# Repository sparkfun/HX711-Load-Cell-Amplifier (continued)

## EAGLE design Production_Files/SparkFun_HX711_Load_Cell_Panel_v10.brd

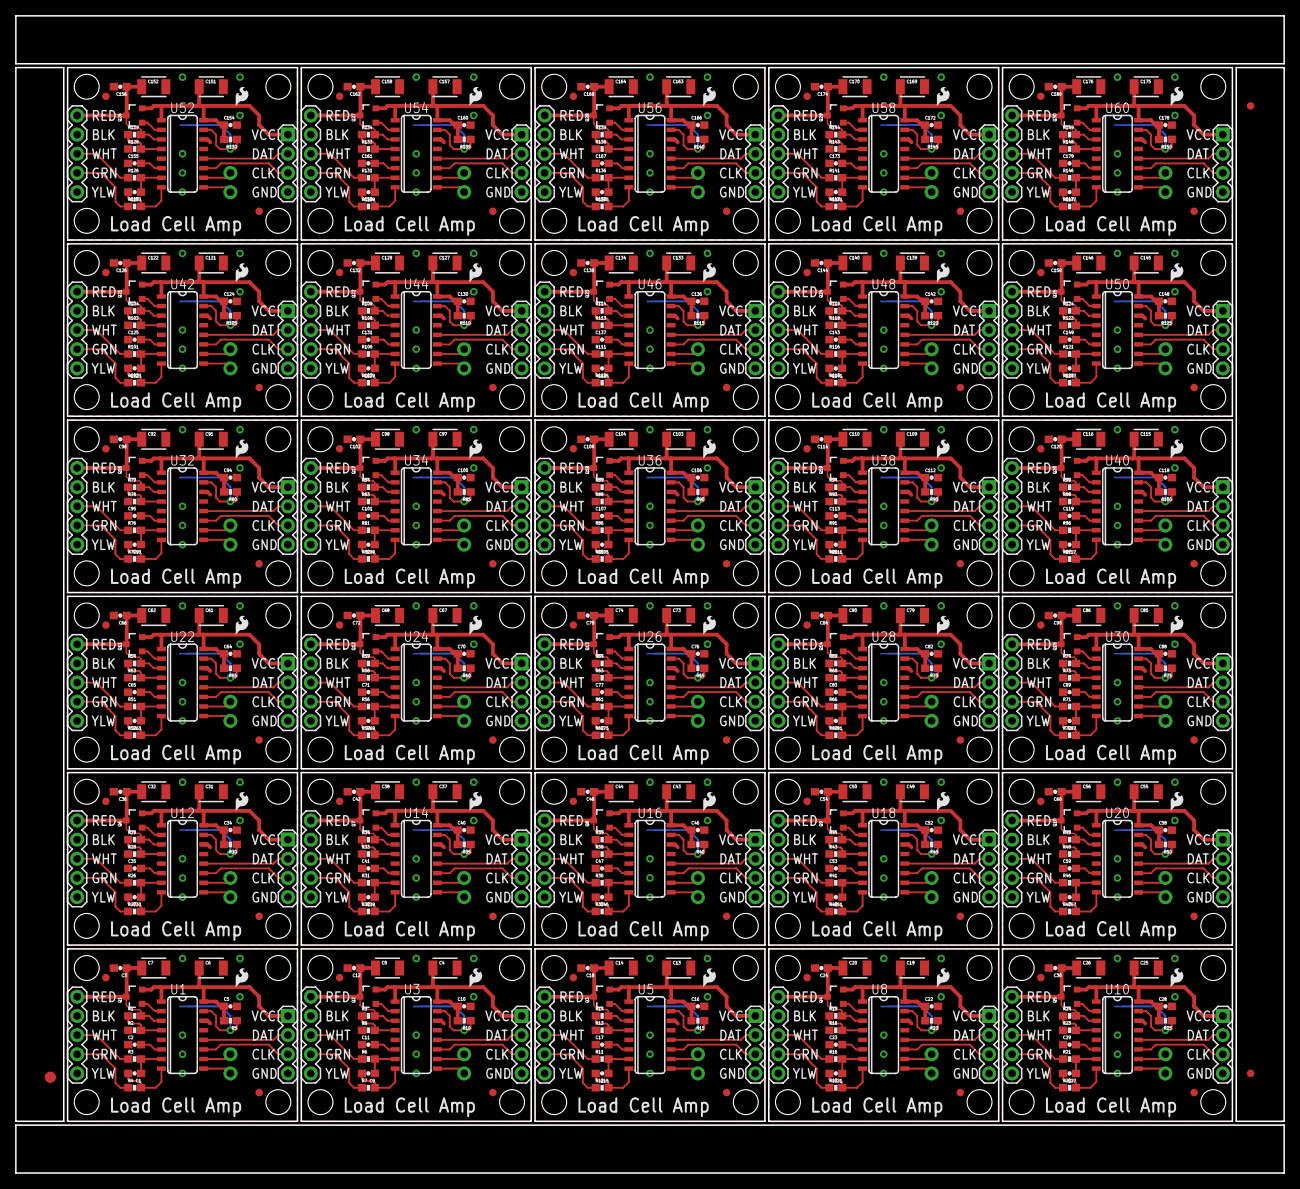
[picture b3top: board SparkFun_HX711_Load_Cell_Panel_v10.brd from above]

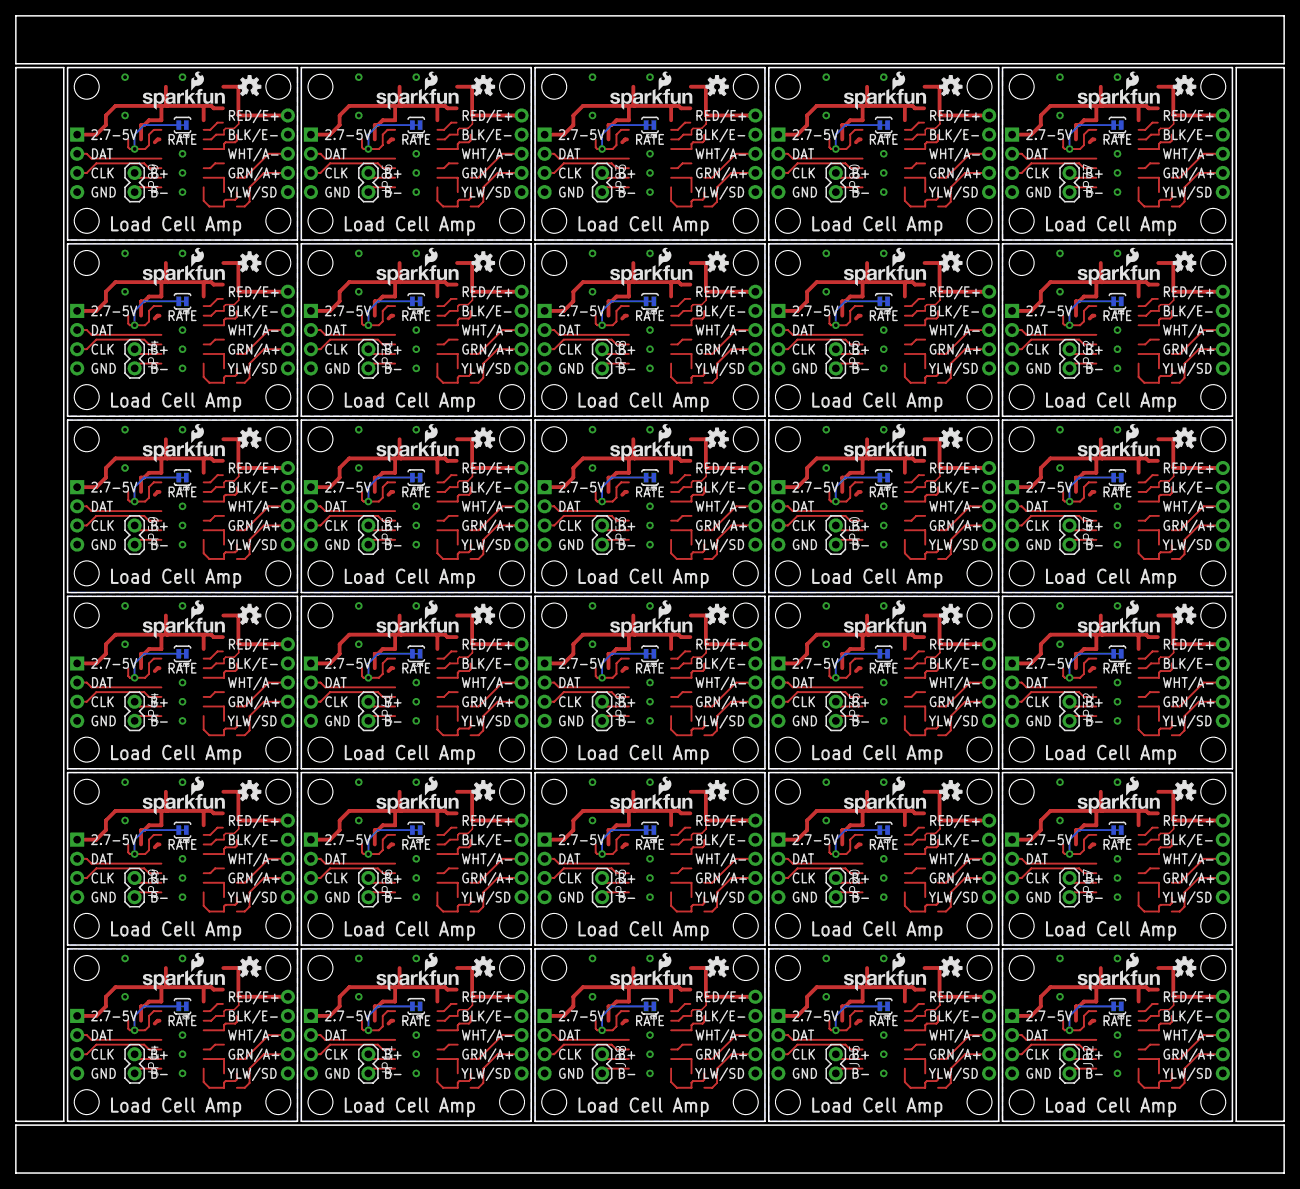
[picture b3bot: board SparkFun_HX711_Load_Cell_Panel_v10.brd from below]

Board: 2 copper layers, 168.1 x 153.4 mm, 783 parts (120 on the bottom side), 450 nets.

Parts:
C1, C2, C3, C5, C9, C10, C11, C12, C15, C16, C17, C18, C21, C22, C23, C24, C27, C28, C29, C30, C33, C34, C35, C36, C39, C40, C41, C42, C45, C46, C47, C48, C51, C52, C53, C54, C57, C58, C59, C60, C63, C64, C65, C66, C69, C70, C71, C72, C75, C76, C77, C78, C81, C82, C83, C84, C87, C88, C89, C90, C93, C94, C95, C96, C99, C100, C101, C102, C105, C106, C107, C108, C111, C112, C113, C114, C117, C118, C119, C120, C123, C124, C125, C126, C129, C130, C131, C132, C135, C136, C137, C138, C141, C142, C143, C144, C147, C148, C149, C150, C153, C154, C155, C156, C159, C160, C161, C162, C165, C166, C167, C168, C171, C172, C173, C174, C177, C178, C179, C180: 0.1uF; 0603-CAP
C4, C6, C7, C8, C13, C14, C19, C20, C25, C26, C31, C32, C37, C38, C43, C44, C49, C50, C55, C56, C61, C62, C67, C68, C73, C74, C79, C80, C85, C86, C91, C92, C97, C98, C103, C104, C109, C110, C115, C116, C121, C122, C127, C128, C133, C134, C139, C140, C145, C146, C151, C152, C157, C158, C163, C164, C169, C170, C175, C176: 10uF; 1210
E$1: FIDUCIAL-1.5X3
E$4, E$5: FIDUCIAL-1X2
FID1, FID2, FID3, FID4, FID5, FID6, FID7, FID8, FID9, FID10, FID11, FID12, FID13, FID14, FID15, FID16, FID17, FID18, FID19, FID20, FID21, FID22, FID23, FID24, FID25, FID26, FID27, FID28, FID29, FID30, FID31, FID32, FID33, FID34, FID35, FID36, FID37, FID38, FID39, FID40, FID41, FID42, FID43, FID44, FID45, FID46, FID47, FID48, FID49, FID50, FID51, FID52, FID53, FID54, FID55, FID56, FID57, FID58, FID59, FID60: FIDUCIAL1X2; FIDUCIAL-1X2
JP1, JP3, JP7, JP10, JP13, JP16, JP19, JP22, JP25, JP28, JP31, JP34, JP37, JP40, JP43, JP46, JP49, JP52, JP55, JP58, JP61, JP64, JP67, JP70, JP73, JP76, JP79, JP82, JP85, JP88: 1X04
JP2, JP5, JP8, JP11, JP14, JP17, JP20, JP23, JP26, JP29, JP32, JP35, JP38, JP41, JP44, JP47, JP50, JP53, JP56, JP59, JP62, JP65, JP68, JP71, JP74, JP77, JP80, JP83, JP86, JP89: 1X02
JP4, JP6, JP9, JP12, JP15, JP18, JP21, JP24, JP27, JP30, JP33, JP36, JP39, JP42, JP45, JP48, JP51, JP54, JP57, JP60, JP63, JP66, JP69, JP72, JP75, JP78, JP81, JP84, JP87, JP90: 1X05
LOGO1, LOGO2, LOGO5, LOGO7, LOGO9, LOGO11, LOGO13, LOGO15, LOGO17, LOGO19, LOGO21, LOGO23, LOGO25, LOGO27, LOGO29, LOGO31, LOGO33, LOGO35, LOGO37, LOGO39, LOGO41, LOGO43, LOGO45, LOGO47, LOGO49, LOGO51, LOGO53, LOGO55, LOGO57, LOGO59: SFE_LOGO_NAME_FLAME.1_INCH; SFE_LOGO_NAME_FLAME_.1
LOGO3, LOGO4, LOGO6, LOGO8, LOGO10, LOGO12, LOGO14, LOGO16, LOGO18, LOGO20, LOGO22, LOGO24, LOGO26, LOGO28, LOGO30, LOGO32, LOGO34, LOGO36, LOGO38, LOGO40, LOGO42, LOGO44, LOGO46, LOGO48, LOGO50, LOGO52, LOGO54, LOGO56, LOGO58, LOGO60: SFE_LOGO_FLAME.1_INCH; SFE_LOGO_FLAME_.1
Q1, Q2, Q3, Q4, Q5, Q6, Q7, Q8, Q9, Q10, Q11, Q12, Q13, Q14, Q15, Q16, Q17, Q18, Q19, Q20, Q21, Q22, Q23, Q24, Q25, Q26, Q27, Q28, Q29, Q30: MMBT4403; SOT23-3
R1, R9, R14, R19, R24, R29, R34, R39, R44, R49, R54, R59, R64, R69, R74, R79, R84, R89, R94, R99, R104, R109, R114, R119, R124, R129, R134, R139, R144, R149: 20K; 0603-RES
R2, R8, R13, R18, R23, R28, R33, R38, R43, R48, R53, R58, R63, R68, R73, R78, R83, R88, R93, R98, R103, R108, R113, R118, R123, R128, R133, R138, R143, R148: 8.2K; 0603-RES
R3, R4, R6, R7, R11, R12, R16, R17, R21, R22, R26, R27, R31, R32, R36, R37, R41, R42, R46, R47, R51, R52, R56, R57, R61, R62, R66, R67, R71, R72, R76, R77, R81, R82, R86, R87, R91, R92, R96, R97, R101, R102, R106, R107, R111, R112, R116, R117, R121, R122, R126, R127, R131, R132, R136, R137, R141, R142, R146, R147: 100; 0603-RES
R5, R10, R15, R20, R25, R30, R35, R40, R45, R50, R55, R60, R65, R70, R75, R80, R85, R90, R95, R100, R105, R110, R115, R120, R125, R130, R135, R140, R145, R150: 10K; 0603-RES
SJ1, SJ2, SJ3, SJ4, SJ5, SJ6, SJ7, SJ8, SJ9, SJ10, SJ11, SJ12, SJ13, SJ14, SJ15, SJ16, SJ17, SJ18, SJ19, SJ20, SJ21, SJ22, SJ23, SJ24, SJ25, SJ26, SJ27, SJ28, SJ29, SJ30: PAD-JUMPER-2-NC_BY_TRACE_YES_SILK
STANDOFF1, STANDOFF2, STANDOFF3, STANDOFF4, STANDOFF5, STANDOFF6, STANDOFF7, STANDOFF8, STANDOFF9, STANDOFF10, STANDOFF11, STANDOFF12, STANDOFF13, STANDOFF14, STANDOFF15, STANDOFF16, STANDOFF17, STANDOFF18, STANDOFF19, STANDOFF20, STANDOFF21, STANDOFF22, STANDOFF23, STANDOFF24, STANDOFF25, STANDOFF26, STANDOFF27, STANDOFF28, STANDOFF29, STANDOFF30, STANDOFF31, STANDOFF32, STANDOFF33, STANDOFF34, STANDOFF35, STANDOFF36, STANDOFF37, STANDOFF38, STANDOFF39, STANDOFF40, STANDOFF41, STANDOFF42, STANDOFF43, STANDOFF44, STANDOFF45, STANDOFF46, STANDOFF47, STANDOFF48, STANDOFF49, STANDOFF50, STANDOFF51, STANDOFF52, STANDOFF53, STANDOFF54, STANDOFF55, STANDOFF56, STANDOFF57, STANDOFF58, STANDOFF59, STANDOFF60, STANDOFF61, STANDOFF62, STANDOFF63, STANDOFF64, STANDOFF65, STANDOFF66, STANDOFF67, STANDOFF68, STANDOFF69, STANDOFF70, STANDOFF71, STANDOFF72, STANDOFF73, STANDOFF74, STANDOFF75, STANDOFF76, STANDOFF77, STANDOFF78, STANDOFF79, STANDOFF80, STANDOFF81, STANDOFF82, STANDOFF83, STANDOFF84, STANDOFF85, STANDOFF86, STANDOFF87, STANDOFF88, STANDOFF89, STANDOFF90, STANDOFF91, STANDOFF92, STANDOFF93, STANDOFF94, STANDOFF95, STANDOFF96, STANDOFF97, STANDOFF98, STANDOFF99, STANDOFF100, STANDOFF101, STANDOFF102, STANDOFF103, STANDOFF104, STANDOFF105, STANDOFF106, STANDOFF107, STANDOFF108, STANDOFF109, STANDOFF110, STANDOFF111, STANDOFF112, STANDOFF113, STANDOFF114, STANDOFF115, STANDOFF116, STANDOFF117, STANDOFF118, STANDOFF119, STANDOFF120: STAND-OFF
U1, U3, U5, U8, U10, U12, U14, U16, U18, U20, U22, U24, U26, U28, U30, U32, U34, U36, U38, U40, U42, U44, U46, U48, U50, U52, U54, U56, U58, U60: HX711; SO16
U2, U4, U6, U7, U9, U11, U13, U15, U17, U19, U21, U23, U25, U27, U29, U31, U33, U35, U37, U39, U41, U43, U45, U47, U49, U51, U53, U55, U57, U59: OSHW-LOGOS; OSHW-LOGO-S

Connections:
A+: JP4.2, R4.1
A+1: JP6.2, R7.1
A+2: JP9.2, R12.1
A+3: JP12.2, R17.1
A+4: JP15.2, R22.1
A+5: JP18.2, R27.1
A+6: JP21.2, R32.1
A+7: JP24.2, R37.1
A+8: JP27.2, R42.1
A+9: JP30.2, R47.1
A+10: JP33.2, R52.1
A+11: JP36.2, R57.1
A+12: JP39.2, R62.1
A+13: JP42.2, R67.1
A+14: JP45.2, R72.1
A+15: JP48.2, R77.1
A+16: JP51.2, R82.1
A+17: JP54.2, R87.1
A+18: JP57.2, R92.1
A+19: JP60.2, R97.1
A+20: JP63.2, R102.1
A+21: JP66.2, R107.1
A+22: JP69.2, R112.1
A+23: JP72.2, R117.1
A+24: JP75.2, R122.1
A+25: JP78.2, R127.1
A+26: JP81.2, R132.1
A+27: JP84.2, R137.1
A+28: JP87.2, R142.1
A+29: JP90.2, R147.1
A-: JP4.3, R3.1
A-1: JP6.3, R6.1
A-2: JP9.3, R11.1
A-3: JP12.3, R16.1
A-4: JP15.3, R21.1
A-5: JP18.3, R26.1
A-6: JP21.3, R31.1
A-7: JP24.3, R36.1
A-8: JP27.3, R41.1
A-9: JP30.3, R46.1
A-10: JP33.3, R51.1
A-11: JP36.3, R56.1
A-12: JP39.3, R61.1
A-13: JP42.3, R66.1
A-14: JP45.3, R71.1
A-15: JP48.3, R76.1
A-16: JP51.3, R81.1
A-17: JP54.3, R86.1
A-18: JP57.3, R91.1
A-19: JP60.3, R96.1
A-20: JP63.3, R101.1
A-21: JP66.3, R106.1
A-22: JP69.3, R111.1
A-23: JP72.3, R116.1
A-24: JP75.3, R121.1
A-25: JP78.3, R126.1
A-26: JP81.3, R131.1
A-27: JP84.3, R136.1
A-28: JP87.3, R141.1
A-29: JP90.3, R146.1
AVDD: C3.1, C7.1, JP4.5, Q1.3, R1.2, U1.3
AVDD1: C8.1, C12.1, JP6.5, Q2.3, R9.2, U3.3
AVDD2: C14.1, C18.1, JP9.5, Q3.3, R14.2, U5.3
AVDD3: C20.1, C24.1, JP12.5, Q4.3, R19.2, U8.3
AVDD4: C26.1, C30.1, JP15.5, Q5.3, R24.2, U10.3
AVDD5: C32.1, C36.1, JP18.5, Q6.3, R29.2, U12.3
AVDD6: C38.1, C42.1, JP21.5, Q7.3, R34.2, U14.3
AVDD7: C44.1, C48.1, JP24.5, Q8.3, R39.2, U16.3
AVDD8: C50.1, C54.1, JP27.5, Q9.3, R44.2, U18.3
AVDD9: C56.1, C60.1, JP30.5, Q10.3, R49.2, U20.3
AVDD10: C62.1, C66.1, JP33.5, Q11.3, R54.2, U22.3
AVDD11: C68.1, C72.1, JP36.5, Q12.3, R59.2, U24.3
AVDD12: C74.1, C78.1, JP39.5, Q13.3, R64.2, U26.3
AVDD13: C80.1, C84.1, JP42.5, Q14.3, R69.2, U28.3
AVDD14: C86.1, C90.1, JP45.5, Q15.3, R74.2, U30.3
AVDD15: C92.1, C96.1, JP48.5, Q16.3, R79.2, U32.3
AVDD16: C98.1, C102.1, JP51.5, Q17.3, R84.2, U34.3
AVDD17: C104.1, C108.1, JP54.5, Q18.3, R89.2, U36.3
AVDD18: C110.1, C114.1, JP57.5, Q19.3, R94.2, U38.3
AVDD19: C116.1, C120.1, JP60.5, Q20.3, R99.2, U40.3
AVDD20: C122.1, C126.1, JP63.5, Q21.3, R104.2, U42.3
AVDD21: C128.1, C132.1, JP66.5, Q22.3, R109.2, U44.3
AVDD22: C134.1, C138.1, JP69.5, Q23.3, R114.2, U46.3
AVDD23: C140.1, C144.1, JP72.5, Q24.3, R119.2, U48.3
AVDD24: C146.1, C150.1, JP75.5, Q25.3, R124.2, U50.3
AVDD25: C152.1, C156.1, JP78.5, Q26.3, R129.2, U52.3
AVDD26: C158.1, C162.1, JP81.5, Q27.3, R134.2, U54.3
AVDD27: C164.1, C168.1, JP84.5, Q28.3, R139.2, U56.3
AVDD28: C170.1, C174.1, JP87.5, Q29.3, R144.2, U58.3
AVDD29: C176.1, C180.1, JP90.5, Q30.3, R149.2, U60.3
B+: JP2.1, U1.10
B+1: JP5.1, U3.10
B+2: JP8.1, U5.10
B+3: JP11.1, U8.10
B+4: JP14.1, U10.10
B+5: JP17.1, U12.10
B+6: JP20.1, U14.10
B+7: JP23.1, U16.10
B+8: JP26.1, U18.10
B+9: JP29.1, U20.10
B+10: JP32.1, U22.10
B+11: JP35.1, U24.10
B+12: JP38.1, U26.10
B+13: JP41.1, U28.10
B+14: JP44.1, U30.10
B+15: JP47.1, U32.10
B+16: JP50.1, U34.10
B+17: JP53.1, U36.10
B+18: JP56.1, U38.10
B+19: JP59.1, U40.10
B+20: JP62.1, U42.10
B+21: JP65.1, U44.10
B+22: JP68.1, U46.10
B+23: JP71.1, U48.10
B+24: JP74.1, U50.10
B+25: JP77.1, U52.10
B+26: JP80.1, U54.10
B+27: JP83.1, U56.10
B+28: JP86.1, U58.10
B+29: JP89.1, U60.10
B-: JP2.2, U1.9
B-1: JP5.2, U3.9
B-2: JP8.2, U5.9
B-3: JP11.2, U8.9
B-4: JP14.2, U10.9
B-5: JP17.2, U12.9
B-6: JP20.2, U14.9
B-7: JP23.2, U16.9
B-8: JP26.2, U18.9
B-9: JP29.2, U20.9
B-10: JP32.2, U22.9
B-11: JP35.2, U24.9
B-12: JP38.2, U26.9
B-13: JP41.2, U28.9
B-14: JP44.2, U30.9
B-15: JP47.2, U32.9
B-16: JP50.2, U34.9
B-17: JP53.2, U36.9
B-18: JP56.2, U38.9
B-19: JP59.2, U40.9
B-20: JP62.2, U42.9
B-21: JP65.2, U44.9
B-22: JP68.2, U46.9
B-23: JP71.2, U48.9
B-24: JP74.2, U50.9
B-25: JP77.2, U52.9
B-26: JP80.2, U54.9
B-27: JP83.2, U56.9
B-28: JP86.2, U58.9
B-29: JP89.2, U60.9
DAT: JP1.2, U1.12
DAT1: JP3.2, U3.12
DAT2: JP7.2, U5.12
DAT3: JP10.2, U8.12
DAT4: JP13.2, U10.12
DAT5: JP16.2, U12.12
DAT6: JP19.2, U14.12
DAT7: JP22.2, U16.12
DAT8: JP25.2, U18.12
DAT9: JP28.2, U20.12
DAT10: JP31.2, U22.12
DAT11: JP34.2, U24.12
DAT12: JP37.2, U26.12
DAT13: JP40.2, U28.12
DAT14: JP43.2, U30.12
DAT15: JP46.2, U32.12
DAT16: JP49.2, U34.12
DAT17: JP52.2, U36.12
DAT18: JP55.2, U38.12
DAT19: JP58.2, U40.12
DAT20: JP61.2, U42.12
DAT21: JP64.2, U44.12
DAT22: JP67.2, U46.12
DAT23: JP70.2, U48.12
DAT24: JP73.2, U50.12
DAT25: JP76.2, U52.12
DAT26: JP79.2, U54.12
DAT27: JP82.2, U56.12
DAT28: JP85.2, U58.12
DAT29: JP88.2, U60.12
GND: C2.1, C3.2, C5.2, C6.2, C7.2, JP1.4, JP4.1, JP4.4, R2.1, SJ2.1, U1.5, U1.14
GND1: C4.2, C8.2, C10.2, C11.1, C12.2, JP3.4, JP6.1, JP6.4, R8.1, SJ1.1, U3.5, U3.14
GND2: C13.2, C14.2, C16.2, C17.1, C18.2, JP7.4, JP9.1, JP9.4, R13.1, SJ3.1, U5.5, U5.14
GND3: C19.2, C20.2, C22.2, C23.1, C24.2, JP10.4, JP12.1, JP12.4, R18.1, SJ4.1, U8.5, U8.14
GND4: C25.2, C26.2, C28.2, C29.1, C30.2, JP13.4, JP15.1, JP15.4, R23.1, SJ5.1, U10.5, U10.14
GND5: C31.2, C32.2, C34.2, C35.1, C36.2, JP16.4, JP18.1, JP18.4, R28.1, SJ6.1, U12.5, U12.14
GND6: C37.2, C38.2, C40.2, C41.1, C42.2, JP19.4, JP21.1, JP21.4, R33.1, SJ7.1, U14.5, U14.14
GND7: C43.2, C44.2, C46.2, C47.1, C48.2, JP22.4, JP24.1, JP24.4, R38.1, SJ8.1, U16.5, U16.14
GND8: C49.2, C50.2, C52.2, C53.1, C54.2, JP25.4, JP27.1, JP27.4, R43.1, SJ9.1, U18.5, U18.14
GND9: C55.2, C56.2, C58.2, C59.1, C60.2, JP28.4, JP30.1, JP30.4, R48.1, SJ10.1, U20.5, U20.14
GND10: C61.2, C62.2, C64.2, C65.1, C66.2, JP31.4, JP33.1, JP33.4, R53.1, SJ11.1, U22.5, U22.14
GND11: C67.2, C68.2, C70.2, C71.1, C72.2, JP34.4, JP36.1, JP36.4, R58.1, SJ12.1, U24.5, U24.14
GND12: C73.2, C74.2, C76.2, C77.1, C78.2, JP37.4, JP39.1, JP39.4, R63.1, SJ13.1, U26.5, U26.14
GND13: C79.2, C80.2, C82.2, C83.1, C84.2, JP40.4, JP42.1, JP42.4, R68.1, SJ14.1, U28.5, U28.14
GND14: C85.2, C86.2, C88.2, C89.1, C90.2, JP43.4, JP45.1, JP45.4, R73.1, SJ15.1, U30.5, U30.14
GND15: C91.2, C92.2, C94.2, C95.1, C96.2, JP46.4, JP48.1, JP48.4, R78.1, SJ16.1, U32.5, U32.14
GND16: C97.2, C98.2, C100.2, C101.1, C102.2, JP49.4, JP51.1, JP51.4, R83.1, SJ17.1, U34.5, U34.14
GND17: C103.2, C104.2, C106.2, C107.1, C108.2, JP52.4, JP54.1, JP54.4, R88.1, SJ18.1, U36.5, U36.14
GND18: C109.2, C110.2, C112.2, C113.1, C114.2, JP55.4, JP57.1, JP57.4, R93.1, SJ19.1, U38.5, U38.14
GND19: C115.2, C116.2, C118.2, C119.1, C120.2, JP58.4, JP60.1, JP60.4, R98.1, SJ20.1, U40.5, U40.14
GND20: C121.2, C122.2, C124.2, C125.1, C126.2, JP61.4, JP63.1, JP63.4, R103.1, SJ21.1, U42.5, U42.14
GND21: C127.2, C128.2, C130.2, C131.1, C132.2, JP64.4, JP66.1, JP66.4, R108.1, SJ22.1, U44.5, U44.14
GND22: C133.2, C134.2, C136.2, C137.1, C138.2, JP67.4, JP69.1, JP69.4, R113.1, SJ23.1, U46.5, U46.14
GND23: C139.2, C140.2, C142.2, C143.1, C144.2, JP70.4, JP72.1, JP72.4, R118.1, SJ24.1, U48.5, U48.14
GND24: C145.2, C146.2, C148.2, C149.1, C150.2, JP73.4, JP75.1, JP75.4, R123.1, SJ25.1, U50.5, U50.14
GND25: C151.2, C152.2, C154.2, C155.1, C156.2, JP76.4, JP78.1, JP78.4, R128.1, SJ26.1, U52.5, U52.14
GND26: C157.2, C158.2, C160.2, C161.1, C162.2, JP79.4, JP81.1, JP81.4, R133.1, SJ27.1, U54.5, U54.14
GND27: C163.2, C164.2, C166.2, C167.1, C168.2, JP82.4, JP84.1, JP84.4, R138.1, SJ28.1, U56.5, U56.14
GND28: C169.2, C170.2, C172.2, C173.1, C174.2, JP85.4, JP87.1, JP87.4, R143.1, SJ29.1, U58.5, U58.14
GND29: C175.2, C176.2, C178.2, C179.1, C180.2, JP88.4, JP90.1, JP90.4, R148.1, SJ30.1, U60.5, U60.14
unnamed: R5.1, SJ2.2, U1.15
unnamed: C1.1, R3.2, U1.7
unnamed: C1.2, R4.2, U1.8
unnamed: Q1.1, U1.2
unnamed: Q2.1, U3.2
unnamed: R1.1, R2.2, U1.4
unnamed: C2.2, U1.6
unnamed: R8.2, R9.1, U3.4
unnamed: C11.2, U3.6
unnamed: R10.1, SJ1.2, U3.15
unnamed: C9.1, R6.2, U3.7
unnamed: C9.2, R7.2, U3.8
unnamed: Q3.1, U5.2
unnamed: R13.2, R14.1, U5.4
unnamed: C17.2, U5.6
unnamed: R15.1, SJ3.2, U5.15
unnamed: C15.1, R11.2, U5.7
unnamed: C15.2, R12.2, U5.8
unnamed: Q4.1, U8.2
unnamed: R18.2, R19.1, U8.4
unnamed: C23.2, U8.6
unnamed: R20.1, SJ4.2, U8.15
unnamed: C21.1, R16.2, U8.7
unnamed: C21.2, R17.2, U8.8
unnamed: Q5.1, U10.2
unnamed: R23.2, R24.1, U10.4
unnamed: C29.2, U10.6
unnamed: R25.1, SJ5.2, U10.15
unnamed: C27.1, R21.2, U10.7
unnamed: C27.2, R22.2, U10.8
unnamed: Q6.1, U12.2
unnamed: R28.2, R29.1, U12.4
unnamed: C35.2, U12.6
unnamed: R30.1, SJ6.2, U12.15
unnamed: C33.1, R26.2, U12.7
unnamed: C33.2, R27.2, U12.8
unnamed: Q7.1, U14.2
unnamed: R33.2, R34.1, U14.4
unnamed: C41.2, U14.6
unnamed: R35.1, SJ7.2, U14.15
unnamed: C39.1, R31.2, U14.7
unnamed: C39.2, R32.2, U14.8
unnamed: Q8.1, U16.2
unnamed: R38.2, R39.1, U16.4
unnamed: C47.2, U16.6
unnamed: R40.1, SJ8.2, U16.15
unnamed: C45.1, R36.2, U16.7
unnamed: C45.2, R37.2, U16.8
unnamed: Q9.1, U18.2
unnamed: R43.2, R44.1, U18.4
unnamed: C53.2, U18.6
unnamed: R45.1, SJ9.2, U18.15
unnamed: C51.1, R41.2, U18.7
unnamed: C51.2, R42.2, U18.8
unnamed: Q10.1, U20.2
unnamed: R48.2, R49.1, U20.4
unnamed: C59.2, U20.6
unnamed: R50.1, SJ10.2, U20.15
unnamed: C57.1, R46.2, U20.7
unnamed: C57.2, R47.2, U20.8
unnamed: Q11.1, U22.2
unnamed: R53.2, R54.1, U22.4
unnamed: C65.2, U22.6
unnamed: R55.1, SJ11.2, U22.15
unnamed: C63.1, R51.2, U22.7
unnamed: C63.2, R52.2, U22.8
unnamed: Q12.1, U24.2
unnamed: R58.2, R59.1, U24.4
unnamed: C71.2, U24.6
unnamed: R60.1, SJ12.2, U24.15
unnamed: C69.1, R56.2, U24.7
unnamed: C69.2, R57.2, U24.8
unnamed: Q13.1, U26.2
unnamed: R63.2, R64.1, U26.4
unnamed: C77.2, U26.6
unnamed: R65.1, SJ13.2, U26.15
unnamed: C75.1, R61.2, U26.7
unnamed: C75.2, R62.2, U26.8
unnamed: Q14.1, U28.2
unnamed: R68.2, R69.1, U28.4
unnamed: C83.2, U28.6
unnamed: R70.1, SJ14.2, U28.15
unnamed: C81.1, R66.2, U28.7
unnamed: C81.2, R67.2, U28.8
unnamed: Q15.1, U30.2
unnamed: R73.2, R74.1, U30.4
unnamed: C89.2, U30.6
unnamed: R75.1, SJ15.2, U30.15
unnamed: C87.1, R71.2, U30.7
unnamed: C87.2, R72.2, U30.8
unnamed: Q16.1, U32.2
unnamed: R78.2, R79.1, U32.4
unnamed: C95.2, U32.6
unnamed: R80.1, SJ16.2, U32.15
unnamed: C93.1, R76.2, U32.7
unnamed: C93.2, R77.2, U32.8
unnamed: Q17.1, U34.2
unnamed: R83.2, R84.1, U34.4
unnamed: C101.2, U34.6
unnamed: R85.1, SJ17.2, U34.15
unnamed: C99.1, R81.2, U34.7
unnamed: C99.2, R82.2, U34.8
unnamed: Q18.1, U36.2
unnamed: R88.2, R89.1, U36.4
unnamed: C107.2, U36.6
unnamed: R90.1, SJ18.2, U36.15
unnamed: C105.1, R86.2, U36.7
unnamed: C105.2, R87.2, U36.8
unnamed: Q19.1, U38.2
unnamed: R93.2, R94.1, U38.4
unnamed: C113.2, U38.6
unnamed: R95.1, SJ19.2, U38.15
unnamed: C111.1, R91.2, U38.7
unnamed: C111.2, R92.2, U38.8
unnamed: Q20.1, U40.2
unnamed: R98.2, R99.1, U40.4
unnamed: C119.2, U40.6
unnamed: R100.1, SJ20.2, U40.15
unnamed: C117.1, R96.2, U40.7
unnamed: C117.2, R97.2, U40.8
unnamed: Q21.1, U42.2
unnamed: R103.2, R104.1, U42.4
unnamed: C125.2, U42.6
unnamed: R105.1, SJ21.2, U42.15
unnamed: C123.1, R101.2, U42.7
unnamed: C123.2, R102.2, U42.8
unnamed: Q22.1, U44.2
unnamed: R108.2, R109.1, U44.4
unnamed: C131.2, U44.6
unnamed: R110.1, SJ22.2, U44.15
unnamed: C129.1, R106.2, U44.7
unnamed: C129.2, R107.2, U44.8
unnamed: Q23.1, U46.2
unnamed: R113.2, R114.1, U46.4
unnamed: C137.2, U46.6
unnamed: R115.1, SJ23.2, U46.15
unnamed: C135.1, R111.2, U46.7
unnamed: C135.2, R112.2, U46.8
unnamed: Q24.1, U48.2
unnamed: R118.2, R119.1, U48.4
unnamed: C143.2, U48.6
unnamed: R120.1, SJ24.2, U48.15
unnamed: C141.1, R116.2, U48.7
unnamed: C141.2, R117.2, U48.8
unnamed: Q25.1, U50.2
unnamed: R123.2, R124.1, U50.4
unnamed: C149.2, U50.6
unnamed: R125.1, SJ25.2, U50.15
unnamed: C147.1, R121.2, U50.7
unnamed: C147.2, R122.2, U50.8
unnamed: Q26.1, U52.2
unnamed: R128.2, R129.1, U52.4
unnamed: C155.2, U52.6
unnamed: R130.1, SJ26.2, U52.15
unnamed: C153.1, R126.2, U52.7
unnamed: C153.2, R127.2, U52.8
unnamed: Q27.1, U54.2
unnamed: R133.2, R134.1, U54.4
unnamed: C161.2, U54.6
unnamed: R135.1, SJ27.2, U54.15
unnamed: C159.1, R131.2, U54.7
unnamed: C159.2, R132.2, U54.8
unnamed: Q28.1, U56.2
unnamed: R138.2, R139.1, U56.4
unnamed: C167.2, U56.6
unnamed: R140.1, SJ28.2, U56.15
unnamed: C165.1, R136.2, U56.7
unnamed: C165.2, R137.2, U56.8
unnamed: Q29.1, U58.2
unnamed: R143.2, R144.1, U58.4
unnamed: C173.2, U58.6
unnamed: R145.1, SJ29.2, U58.15
unnamed: C171.1, R141.2, U58.7
unnamed: C171.2, R142.2, U58.8
unnamed: Q30.1, U60.2
unnamed: R148.2, R149.1, U60.4
unnamed: C179.2, U60.6
unnamed: R150.1, SJ30.2, U60.15
unnamed: C177.1, R146.2, U60.7
unnamed: C177.2, R147.2, U60.8
SCK: JP1.3, U1.11
SCK1: JP3.3, U3.11
SCK2: JP7.3, U5.11
SCK3: JP10.3, U8.11
SCK4: JP13.3, U10.11
SCK5: JP16.3, U12.11
SCK6: JP19.3, U14.11
SCK7: JP22.3, U16.11
SCK8: JP25.3, U18.11
SCK9: JP28.3, U20.11
SCK10: JP31.3, U22.11
SCK11: JP34.3, U24.11
SCK12: JP37.3, U26.11
SCK13: JP40.3, U28.11
SCK14: JP43.3, U30.11
SCK15: JP46.3, U32.11
SCK16: JP49.3, U34.11
SCK17: JP52.3, U36.11
SCK18: JP55.3, U38.11
SCK19: JP58.3, U40.11
SCK20: JP61.3, U42.11
SCK21: JP64.3, U44.11
SCK22: JP67.3, U46.11
SCK23: JP70.3, U48.11
SCK24: JP73.3, U50.11
SCK25: JP76.3, U52.11
SCK26: JP79.3, U54.11
SCK27: JP82.3, U56.11
SCK28: JP85.3, U58.11
SCK29: JP88.3, U60.11
VCC: C5.1, C6.1, JP1.1, Q1.2, R5.2, U1.1, U1.16
VCC1: C4.1, C10.1, JP3.1, Q2.2, R10.2, U3.1, U3.16
VCC2: C13.1, C16.1, JP7.1, Q3.2, R15.2, U5.1, U5.16
VCC3: C19.1, C22.1, JP10.1, Q4.2, R20.2, U8.1, U8.16
VCC4: C25.1, C28.1, JP13.1, Q5.2, R25.2, U10.1, U10.16
VCC5: C31.1, C34.1, JP16.1, Q6.2, R30.2, U12.1, U12.16
VCC6: C37.1, C40.1, JP19.1, Q7.2, R35.2, U14.1, U14.16
VCC7: C43.1, C46.1, JP22.1, Q8.2, R40.2, U16.1, U16.16
VCC8: C49.1, C52.1, JP25.1, Q9.2, R45.2, U18.1, U18.16
VCC9: C55.1, C58.1, JP28.1, Q10.2, R50.2, U20.1, U20.16
VCC10: C61.1, C64.1, JP31.1, Q11.2, R55.2, U22.1, U22.16
VCC11: C67.1, C70.1, JP34.1, Q12.2, R60.2, U24.1, U24.16
VCC12: C73.1, C76.1, JP37.1, Q13.2, R65.2, U26.1, U26.16
VCC13: C79.1, C82.1, JP40.1, Q14.2, R70.2, U28.1, U28.16
VCC14: C85.1, C88.1, JP43.1, Q15.2, R75.2, U30.1, U30.16
VCC15: C91.1, C94.1, JP46.1, Q16.2, R80.2, U32.1, U32.16
VCC16: C97.1, C100.1, JP49.1, Q17.2, R85.2, U34.1, U34.16
VCC17: C103.1, C106.1, JP52.1, Q18.2, R90.2, U36.1, U36.16
VCC18: C109.1, C112.1, JP55.1, Q19.2, R95.2, U38.1, U38.16
VCC19: C115.1, C118.1, JP58.1, Q20.2, R100.2, U40.1, U40.16
VCC20: C121.1, C124.1, JP61.1, Q21.2, R105.2, U42.1, U42.16
VCC21: C127.1, C130.1, JP64.1, Q22.2, R110.2, U44.1, U44.16
VCC22: C133.1, C136.1, JP67.1, Q23.2, R115.2, U46.1, U46.16
VCC23: C139.1, C142.1, JP70.1, Q24.2, R120.2, U48.1, U48.16
VCC24: C145.1, C148.1, JP73.1, Q25.2, R125.2, U50.1, U50.16
VCC25: C151.1, C154.1, JP76.1, Q26.2, R130.2, U52.1, U52.16
VCC26: C157.1, C160.1, JP79.1, Q27.2, R135.2, U54.1, U54.16
VCC27: C163.1, C166.1, JP82.1, Q28.2, R140.2, U56.1, U56.16
VCC28: C169.1, C172.1, JP85.1, Q29.2, R145.2, U58.1, U58.16
VCC29: C175.1, C178.1, JP88.1, Q30.2, R150.2, U60.1, U60.16

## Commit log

2014-11-17 :space_invader: Added .gitattributes & .gitignore files
2014-11-17 Hardware is ready for protos.
    Passed the QC checklist.
2014-11-19 Changes from initial QC checklist. Adding datasheet.
2014-11-20 Example firmware is ready. Moved datasheet.
2014-11-24 Spread out 0603 components and fixed silk. See issue 1.
2014-11-26 Broke out channel B. Adjusted some traces.
2014-11-26 Fix issue #3. Straightened traces out of SMD pads.
2014-12-04 Silk label adjustment. Added cnt for shielding (yellow).
    Some load cells have a 5th wire that is yellow that shields the four
    wires. Added a ground connection for this 5th wire.
2014-12-07 Change AVDD resistors to output closer to 5V
2015-01-19 Fixing issues #6.
2015-01-26 Fixed feedback from eng review.
    Moved VCC trace out of tKeepout. Fixed 4-way junction on schematic.
    Moved schematic part for standoff holes to proper location.
2015-01-30 Moving all headers onto horizontal grid.
2015-01-30 Extraneous layers removed.
2015-03-03 v10 panel created
2015-06-11 Readme update
2016-03-22 Revision 11 changes
    -Added 3.3uH inductor, this should allow for greater resolution in the
    HX711 ADC.
    -Separated analog and digital supply voltage, which allows 3.3V uCs to
    communicate without additional hardware.
    -Added 0.1uF cap to digital supply.
2016-03-29 Revision 11 (Update)
    Corrected net label from N$5 to AVDD.
2016-05-09 Rotated copper for version number
    Now matches with board silk
2016-05-10 deleted old panel
2016-05-10 V11 Update
    Removed spaces from file names
    Fixed silk causing CAM errors
2016-05-10 created panel v11
2019-05-15 Updated Schematic and Datasheet
    -Updated to the newest datasheet for the HX711 which corrected the equation from AVDD = VBG(R1+R2)/R1 to AVDD = VBG(R1+R2)/R2.
    -Updated the schematic with the correct equation
2019-06-14 Update for HX711 v0.7.2
    The HX711 library now only has a default constructor, begin() must
    be used to initialize DOUT, PD_SCK and GAIN.
2019-06-25 Fix examples to match rev on HX711 library
